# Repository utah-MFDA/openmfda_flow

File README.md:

# OpenMFDA (Microfluidic Design Automation) – Quick start
We are excited to help members of the community test and use this software. If you are interested we are happy to help you get started, please email ashton.snelgrove@utah.edu.

This document should help with providing setup and run the software flow for OpenMFDA with the
supplied code to run that smart toilet chip. For the most up to date version clone the repo at
https://github.com/utah-MFDA/openmfda_flow.

## Setup

### Submodules

If pulled from github, this repository contains submodule links to design kits and tools. Make
sure to run `git submodule update --init --recursive` after cloning or updating to ensure that
the submodules are up to date.

### Prerequisites Linux based systems

The following external tools are required.
- OpenROAD
- KLayout
- Xyce (7.8)
    - must be built from source with the ADMS plugin
    - ADMS (2.3.7)
- OpenSCAD
- python3
- make

The OpenROAD tool can be downloaded at https://github.com/The-OpenROAD-Project/OpenROAD.
Xyce can be built from https://github.com/Xyce/Xyce. Be sure to build with the ADMS plugin.

By default, the tools are invoked using the $PATH search variable.

Environment variables can be set to specify a specific location for the tools.

### Python environment

Python package dependencies can be installed using the system package manager, or using a virtual environment.
To create a virtual environment and install the tool dependencies, run the following commands.

```
python3 -m venv env
source env/bin/activate
pip3 install -r python-requirements.txt
```

This will create a directory `env` containing the python environment and libraries. To activate
the environment you will need to run `source env/bin/activate` before using the flow.
For more information about virtual environments, see https://docs.python.org/3/library/venv.html

## Prerequisites for Docker base implementation

We have a developed Docker based implementation for deployment that can work on
non-linux systems.

### Software requirements
- Docker
    - Recommended: https://docs.docker.com/desktop/
- WSL
    - https://learn.microsoft.com/en-us/windows/wsl/install
- Python3
- Recommended: OpenSCAD

## Running the flow

### Linux based systems

Once configured (as demonstrated in the next section), the flow is invoked with the `make` command.

Specifying the design
The design being operated on is specified using the `DESIGN` variable, matching the design
name used during configuration. This can be set by:

- The design can be specified when invoking `make`, for example `make DESIGN=smart_toilet`.
- The design can be specified once in an environment variable `export DESIGN=smart_toilet`,
	then subsequent invocations using `make -e`.
- The `DESIGN` variable can be set in the `Makefile` in the root of the directory.

### Running the flow

To run the complete flow, invoke `make` (with the design variable specified as shown in the previous section).
This will run all steps in the flow and generate a .zip archive containing all output files.

To run placement and routing, invoke `make pnr`

To generate the device 3D model, invoke `make render`

To generate flow analysis files of the design, invoke `make simulate`

To remove all generated files, invoke `make clean`

## For non-linux based system - Docker based implementation

For non-linux based system a script to run the flow within a docker image with the necessary software is provided.
This must be run within a windows WSL shell (a linux shell within windows) for windows systems, instructions
to install WSL on windows can be found at, https://learn.microsoft.com/en-us/windows/wsl/install

To get started you can simply run the command:

```
python3 run_mfda_docker.py –design smart_toilet
```

This will, in not already, download the docker image, and run the demo, smart toilet chip, design.
The Docker image will contain the necessary software and python packages to run the flow.

# Configuration

## Quick start configuration

Place your verilog netlist in the root directory of the flow.

Create a copy of the `demo_configure.py` script or create a new file with the following.

```
from openmfda_flow import *

verilog_file = "demo.v"
design_name = "demo"
platform = "h.r.3.3"
pins = [[None for i in range(0,8)] for j in range(0,4)]
pins[0][1] = "soln1"
pins[0][2] = "soln2"
pins[0][3] = "soln3"
pins[1][7] = "out"

generate_config(verilog_file, design_name, pin_names=pins, platform=platform)
```

Modify your copy, specifying the `verilog_file` and `design_name`.

For each input/output pins from your verilog file, add an entry in the array in row/column format. This will assign the pin to the port of the interface.

Invoke your script like `python3 demo_configure.py`, which will generate configuration files.

After the configuration is created, the flow can be run by invoking `make DESIGN=demo`.

Once configured, verilog design and configuration files can be modified as described in the next section. Verilog files are located in `openroad_flow/designs/src/{DESIGN}`

## Manual configuration

To manually configure a flow, the following steps are taken:

1. Start by creating a new design with this path structure
    - openroad_flow/designs/(platform)/(design name)
2. Within the folder above, three files need to be generated:
   ./config.mk, ./constraint.sdc, and ./io_constraints.tcl.
   Designs are included for reference.
    - ./config.mk - this contains variables that specify the
      design name, platform, relevant design paths, and floor
      planning parameters such as die size (MF chip size) and
      core size (legal placement and route area).
    - ./constraint.sdc - only contains the design name.
      Critical file in EDA but not used in the current flow of
      MFDA.
    - ./io_constraints.tcl - this specifies where the I/Os of
      the MF chip are physically located. If using the
      flushing chip automatically generated in the flow, the
      I/Os must be configured such as in
      /openroad_flow/designs/mfda/smart_toilet/io_constraints.tcl
      for correct allignment with the flushing chip. Otherwise,
      the I/Os must be placed at the edge of the device and
      pinholes will automatically added for tubing.
3. The chips are described using Verilog HDL netlist scripting.
   The netlist description is structured like
   /openroad_flow/designs/src/(design)/(design).v.
   This netlist describes the I/Os, what components are used,
   and how they are all connected.
4. In /openroad_flow/Makefile, the *DESIGN_CONFIG* variable
   must be the path to the /config.mk file described in step 2.
5. The 3D configuration is setup in this path structure,
   /scad_flow/designs/(platform)/(design name). Within
   this folder are two files: ./config.mk and the optional file
   ./dimm.csv.
   - ./config.mk - This file contains several variable that
     specify the 3D parameters of the MF chip as well as the printer
     properties such as physical pixel and layer size.
   - ./dimm.csv - this is an optional file which specifies dimensions
     for the interconnect channels between components and I/Os. The format
     should be as follows:
     ```
     For component and I/O interconnects:

     pin_name,horizontal_channel_width,vertical_channel_width,channel_height

     For I/Os (connecting to the flushing chip through the interconnect device):

     pin_name,square_side_width
     ```
     All widths are integer number of pixels and heights are integer number of
     layers.
6. After all the files are added for the design with the
   parameters specified, the entire flow can be completed through
   the Makefile in /Makefile
   ```
   make DESIGN=demo
   ```

## Expected output

We expect during program runtime that the terminal will print the logs for each of
the steps to be completed in the program. Several design files for each step of the
physical design process will be in the `flow/results/<design_name>/base` directory.
The final .scad file that is located in the `flow/results/<design_name>/base` which will
be named `<name of your design>_base.scad` can be loaded into OpenSCAD to render the final
results. The simulation evaluation output will be inside the flow/results/simulation/Chem_Eval.csv`
directory and any probe data will be in `flow/results/simulation/<design_name>_xyceOut.csv`.

Instructions for use on submitted data
To run the program on the smart toilet data simply run.

```
cd flow && make -e DESIGN=smart_toilet
```

or for docker implementation

```
python3 run_mfda_docker.py -–design smart_toilet
```

Results should be located in the `flow/results/smart_toilet/base` directory.

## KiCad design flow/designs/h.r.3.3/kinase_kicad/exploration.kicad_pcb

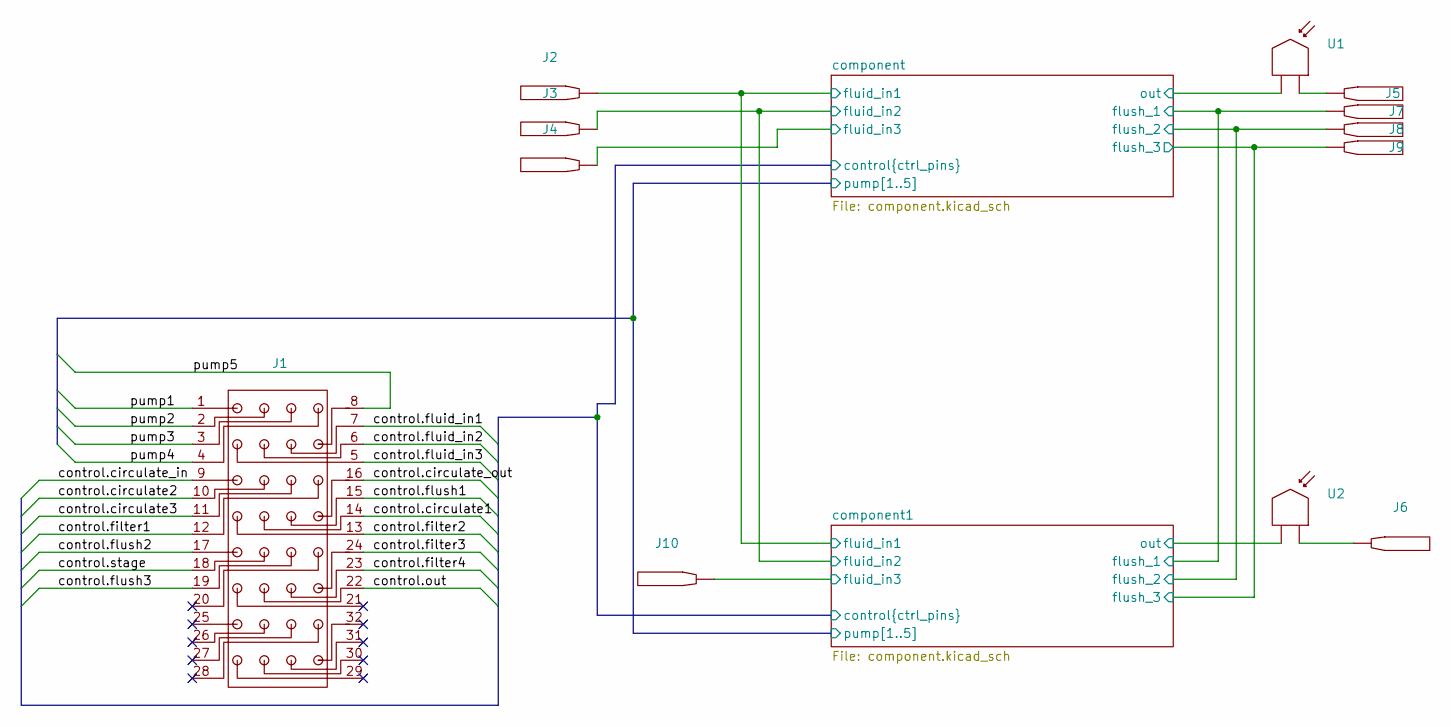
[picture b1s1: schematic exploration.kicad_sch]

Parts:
J1: LQFP-32_7x7mm_P0.8mm
J2, J3, J4, J5, J6, J7, J8, J9, J10: Pin_D1.0mm_L10.0mm
U1, U2: PinHeader_1x02_P2.54mm_Vertical

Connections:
/component1/fluid_in3: J10.1 (connect); also elsewhere on the board
/component1/out: U2.2 (out); also elsewhere on the board
/component/control.circulate1: J1.14; also elsewhere on the board
/component/control.circulate2: J1.10; also elsewhere on the board
/component/control.circulate3: J1.11; also elsewhere on the board
/component/control.circulate_in: J1.9; also elsewhere on the board
/component/control.circulate_out: J1.16; also elsewhere on the board
/component/control.filter1: J1.12; also elsewhere on the board
/component/control.filter2: J1.13; also elsewhere on the board
/component/control.filter3: J1.24; also elsewhere on the board
/component/control.filter4: J1.23; also elsewhere on the board
/component/control.fluid_in1: J1.7; also elsewhere on the board
/component/control.fluid_in2: J1.6; also elsewhere on the board
/component/control.fluid_in3: J1.5; also elsewhere on the board
/component/control.flush1: J1.15; also elsewhere on the board
/component/control.flush2: J1.17; also elsewhere on the board
/component/control.flush3: J1.19; also elsewhere on the board
/component/control.out: J1.22; also elsewhere on the board
/component/control.stage: J1.18; also elsewhere on the board
/component/fluid_in1: J2.1 (connect); also elsewhere on the board
/component/fluid_in2: J3.1 (connect); also elsewhere on the board
/component/fluid_in3: J4.1 (connect); also elsewhere on the board
/component/flush_1: J7.1 (connect); also elsewhere on the board
/component/flush_2: J8.1 (connect); also elsewhere on the board
/component/flush_3: J9.1 (connect); also elsewhere on the board
/component/out: U1.2 (out); also elsewhere on the board
/component/pump1: J1.1; also elsewhere on the board
/component/pump2: J1.2; also elsewhere on the board
/component/pump3: J1.3; also elsewhere on the board
/component/pump4: J1.4; also elsewhere on the board
/component/pump5: J1.8; also elsewhere on the board
unnamed: J5.1 (connect), U1.1 (in)
unnamed: J6.1 (connect), U2.1 (in)

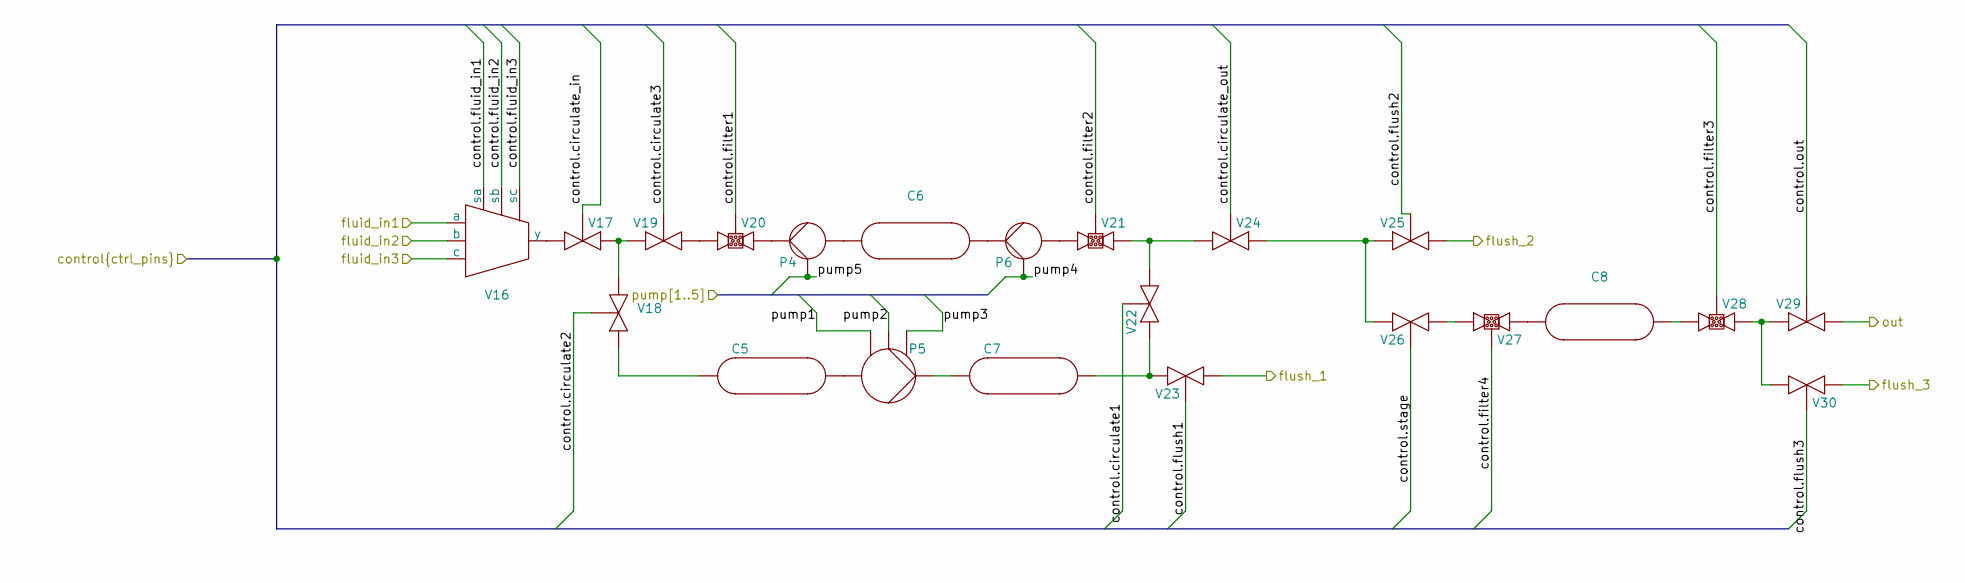
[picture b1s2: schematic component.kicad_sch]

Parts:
C5, C6, C7, C8: R_2010_5025Metric
P4, P6: PinHeader_1x03_P2.54mm_Vertical
P5: PinHeader_1x05_P2.54mm_Vertical
V16: HSOP-8-1EP_3.9x4.9mm_P1.27mm_EP2.41x3.1mm_ThermalVias
V17, V18, V19, V20, V21, V22, V23, V24, V25, V26, V27, V28, V29, V30: Potentiometer_ACP_CA6-VSMD_Vertical

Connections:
/component1/fluid_in3: V16.3 (c); also elsewhere on the board
/component1/out: V29.2 (right); also elsewhere on the board
/component/control.circulate1: V22.3 (control); also elsewhere on the board
/component/control.circulate2: V18.3 (control); also elsewhere on the board
/component/control.circulate3: V19.3 (control); also elsewhere on the board
/component/control.circulate_in: V17.3 (control); also elsewhere on the board
/component/control.circulate_out: V24.3 (control); also elsewhere on the board
/component/control.filter1: V20.3 (control); also elsewhere on the board
/component/control.filter2: V21.3 (control); also elsewhere on the board
/component/control.filter3: V28.3 (control); also elsewhere on the board
/component/control.filter4: V27.3 (control); also elsewhere on the board
/component/control.fluid_in1: V16.4 (sa); also elsewhere on the board
/component/control.fluid_in2: V16.5 (sb); also elsewhere on the board
/component/control.fluid_in3: V16.6 (sc); also elsewhere on the board
/component/control.flush1: V23.3 (control); also elsewhere on the board
/component/control.flush2: V25.3 (control); also elsewhere on the board
/component/control.flush3: V30.3 (control); also elsewhere on the board
/component/control.out: V29.3 (control); also elsewhere on the board
/component/control.stage: V26.3 (control); also elsewhere on the board
/component/fluid_in1: V16.1 (a); also elsewhere on the board
/component/fluid_in2: V16.2 (b); also elsewhere on the board
/component/flush_1: V23.2 (right); also elsewhere on the board
/component/flush_2: V25.2 (right); also elsewhere on the board
/component/flush_3: V30.1 (left); also elsewhere on the board
/component/pump1: P5.3 (pump_1); also elsewhere on the board
/component/pump2: P5.4 (pump_2); also elsewhere on the board
/component/pump3: P5.5 (pump_3); also elsewhere on the board
/component/pump4: P6.3 (pump_1); also elsewhere on the board
/component/pump5: P4.3 (pump_1); also elsewhere on the board
unnamed: C5.1 (in), V18.1 (left)
unnamed: C5.2 (out), P5.1 (in)
unnamed: C6.1 (in), P6.2 (out)
unnamed: C6.2 (out), P4.1 (in)
unnamed: C7.1 (in), P5.2 (out)
unnamed: C7.2 (out), V22.1 (left), V23.1 (left)
unnamed: C8.1 (in), V27.1 (in)
unnamed: C8.2 (out), V28.2 (out)
unnamed: P4.2 (out), V20.1 (in)
unnamed: P6.1 (in), V21.2 (out)
unnamed: V16.7 (y), V17.2 (right)
unnamed: V17.1 (left), V18.2 (right), V19.1 (left)
unnamed: V19.2 (right), V20.2 (out)
unnamed: V21.1 (in), V22.2 (right), V24.2 (right)
unnamed: V24.1 (left), V25.1 (left), V26.1 (left)
unnamed: V26.2 (right), V27.2 (out)
unnamed: V28.1 (in), V29.1 (left), V30.2 (right)

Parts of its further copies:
C1, C2, C3, C4: R_2010_5025Metric
P1, P3: PinHeader_1x03_P2.54mm_Vertical
P2: PinHeader_1x05_P2.54mm_Vertical
V1: HSOP-8-1EP_3.9x4.9mm_P1.27mm_EP2.41x3.1mm_ThermalVias
V2, V3, V4, V5, V6, V7, V8, V9, V10, V11, V12, V13, V14, V15: Potentiometer_ACP_CA6-VSMD_Vertical

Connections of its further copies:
/component/control.circulate1: V7.3 (control); also elsewhere on the board
/component/control.circulate2: V3.3 (control); also elsewhere on the board
/component/control.circulate3: V4.3 (control); also elsewhere on the board
/component/control.circulate_in: V2.3 (control); also elsewhere on the board
/component/control.circulate_out: V9.3 (control); also elsewhere on the board
/component/control.filter1: V5.3 (control); also elsewhere on the board
/component/control.filter2: V6.3 (control); also elsewhere on the board
/component/control.filter3: V13.3 (control); also elsewhere on the board
/component/control.filter4: V12.3 (control); also elsewhere on the board
/component/control.fluid_in1: V1.4 (sa); also elsewhere on the board
/component/control.fluid_in2: V1.5 (sb); also elsewhere on the board
/component/control.fluid_in3: V1.6 (sc); also elsewhere on the board
/component/control.flush1: V8.3 (control); also elsewhere on the board
/component/control.flush2: V10.3 (control); also elsewhere on the board
/component/control.flush3: V15.3 (control); also elsewhere on the board
/component/control.out: V14.3 (control); also elsewhere on the board
/component/control.stage: V11.3 (control); also elsewhere on the board
/component/fluid_in1: V1.1 (a); also elsewhere on the board
/component/fluid_in2: V1.2 (b); also elsewhere on the board
/component/fluid_in3: V1.3 (c); also elsewhere on the board
/component/flush_1: V8.2 (right); also elsewhere on the board
/component/flush_2: V10.2 (right); also elsewhere on the board
/component/flush_3: V15.1 (left); also elsewhere on the board
/component/out: V14.2 (right); also elsewhere on the board
/component/pump1: P2.3 (pump_1); also elsewhere on the board
/component/pump2: P2.4 (pump_2); also elsewhere on the board
/component/pump3: P2.5 (pump_3); also elsewhere on the board
/component/pump4: P3.3 (pump_1); also elsewhere on the board
/component/pump5: P1.3 (pump_1); also elsewhere on the board
unnamed: C1.1 (in), V3.1 (left)
unnamed: C1.2 (out), P2.1 (in)
unnamed: C2.1 (in), P3.2 (out)
unnamed: C2.2 (out), P1.1 (in)
unnamed: C3.1 (in), P2.2 (out)
unnamed: C3.2 (out), V7.1 (left), V8.1 (left)
unnamed: C4.1 (in), V12.1 (in)
unnamed: C4.2 (out), V13.2 (out)
unnamed: P1.2 (out), V5.1 (in)
unnamed: P3.1 (in), V6.2 (out)
unnamed: V1.7 (y), V2.2 (right)
unnamed: V2.1 (left), V3.2 (right), V4.1 (left)
unnamed: V4.2 (right), V5.2 (out)
unnamed: V6.1 (in), V7.2 (right), V9.2 (right)
unnamed: V9.1 (left), V10.1 (left), V11.1 (left)
unnamed: V11.2 (right), V12.2 (out)
unnamed: V13.1 (in), V14.1 (left), V15.2 (right)

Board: 2 copper layers, 56 parts (0 on the bottom side), 67 nets, no tracks yet.

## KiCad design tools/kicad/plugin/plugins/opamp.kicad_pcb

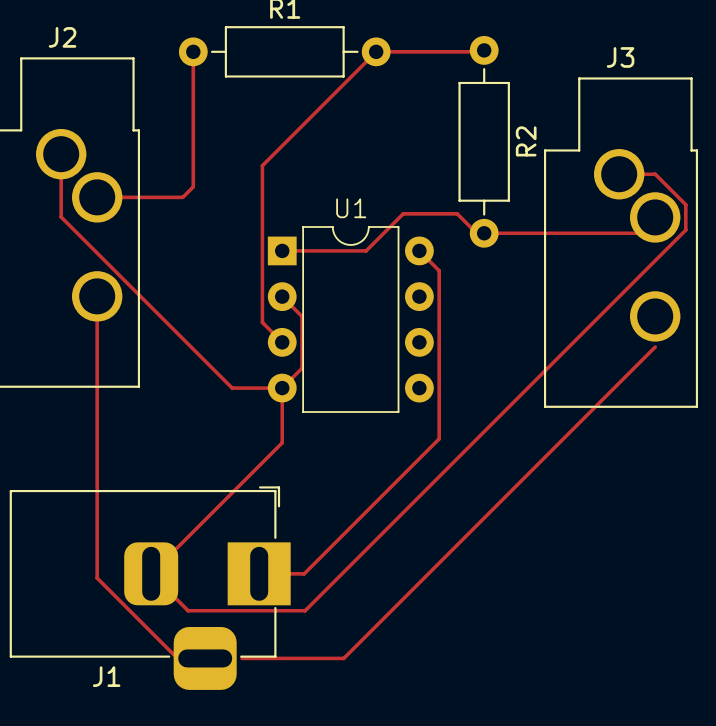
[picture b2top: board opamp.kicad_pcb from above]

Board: 2 copper layers, 6 parts (0 on the bottom side), 5 nets.

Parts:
J1: Barrel_Jack; BarrelJack_Horizontal
J2, J3: AudioJack2; Jack_3.5mm_CUI_SJ1-3533NG_Horizontal_CircularHoles
R1, R2: 100k; R_Axial_DIN0207_L6.3mm_D2.5mm_P10.16mm_Horizontal
U1: TL072; DIP-8_W7.62mm

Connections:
+5V: J1.1, U1.8 (V+)
/result: J3.T, R2.2, U1.1
/signal: J2.T, R1.1
GND: J1.2, J2.S, J3.S, U1.2 (-), U1.4 (V-)
unnamed: R1.2, R2.1, U1.3 (+)

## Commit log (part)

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2024-06-07 python version
2024-06-07 demo with all replace vars
2024-06-07 local updates
2024-06-07 update writeSpice to master
2024-06-10 fix scad sign bug
2024-06-10 Initial kicad network parsing
2024-06-10 Add simulation to flow makefile
2024-06-11 Latest fixes to HR33 pdk
2024-06-13 Complete flow working with simulation and library building
2024-06-13 Basic kicad schematic netlist extraction.
2024-06-18 Initial conversion script from DEF to kicad board.
2024-07-10 src formating and git mods del
2024-07-10 testing platform and OR changes
2024-08-07 major simulation changes, dimm_file ref fixes, openmfda_flow.py changes
2024-08-09 major fixes to generator class
2024-08-27 pcell module and xyce code fixes
2024-08-27 Add pcbnew based conversion scripts
2024-08-28 WX exploration
2024-09-12 Create script to generate kicad footprint library from LEF files.
2024-09-12 Remove debugging and local configuration from lef_to_footprint.
2024-09-12 Remove local test config for main in def_to_pcbnew and def_to_board
2024-09-18 fixes to xyce_flow and scad_flow
2024-09-18 changes to openmfda_class
2024-09-19 join '_' fix to runMFDASim
2024-09-19 OR parsing files
2024-09-20 Add scripts to generate a platform with different number of metal layers.
2024-09-20 Make log directories for our tools actually go to the logs directory.
2024-09-26 init pkg on main branch
2024-10-17 various tool fixes, scad_gen
2024-10-22 Remove reference to networkx
2024-10-24 Fix argparse for consistency in kicad scripts
2024-10-24 Formatting text for kicad footprint generator.
2024-10-25 Set the text type to 'user' for the pin labels when converting footprint.
2024-10-25 Cleaning and fixed hard coded definitions
2024-10-26 merged with fixed version of generator render
2024-11-01 update to submodules
2024-11-01 py src changes and updates to PCell definitions
2024-11-01 added extra scad files to include in the flow
2024-11-04 changes to pcell config.mk
2024-11-05 Added PCELL as dep to floorplan
2024-11-12 Get the correct field from pcbnew for the footprint id in pcbnew-to-verilog
2024-11-20 Remove missing submodule in tools/simulation
2024-11-20 Use correct layer height variable in slicer configuration.
2024-12-05 Update tcl scripts to handle a macro and pad placement scripts
2024-12-05 Setup kinase_activity 2 variant to use explicitly placed chambers and pads.
2024-12-10 Update submodules to fix broken inner modules.
2025-01-10 WIP plugin
2025-01-17 Kinase example macro and pad placement using latest openroad commands.
2025-01-21 WIP export happy: :
2025-01-22 WIP PNR working.
2025-01-23 updates to render gen v2 and helper scripts
2025-01-31 Add kicad page offset
2025-01-31 Add xvfb command variable.
2025-01-31 Create kicad layer names and vias use correct ids.
2025-02-03 Added intersection detection, rm unneeded comments
2025-02-03 devel changes for main flow
2025-02-03 now tracks a stable branch
2025-02-03 def load and export functions, changes to iteration implementation
2025-02-04 Write locked Kicad footprints as explicit placed macro.
2025-02-04 Remove report call missing from latest openroad.
2025-02-06 Fix orientation in the lef to kicad footprint conversion script.
2025-02-10 Update kinase_activity_2 to use new openroad syntax and switch from bump pad to pin. Bump pads generate but special nets are not routed.
2025-02-10 Switch to Brady's scad generator, which is most up to date with pdk changes.
2025-03-15 addition to tcl scripts, fixes to py code
2025-04-14 Lots of clean up, more examples. Added Docker implementation
2025-04-17 write out def
2025-04-18 Added make script
2025-04-21 v0.1 of route fix
2025-04-24 Fix to pcell gen
2025-04-28 Files prior to updating tools/scad_render directory
2025-04-29 Working flow with Python script, issues with Tcl implmentation
2025-05-06 fixes to silent, small mk file chg, src mnt docker
2025-05-07 update to simulation
2025-05-08 Parse verilog models
2025-05-23 DEF_FIX changes
2025-05-29 fixes to replace iter
2025-06-04 grt script fix with added pin and routing size def to scad
2025-06-04 fixed routing size arg
2025-06-17 fix simulation branch ref and gitmodules reference
2025-06-17 Fixed Makefile ref for simulation
2025-06-17 updated component file
2025-06-22 inluded some support python code, and old lef lib
2025-06-22 update pdk ref, lib link fix, test script fix
2025-06-26 fixes to req and update docs
2025-06-26 small run_dock fix
2025-07-03 WIP fixing sizes
2025-07-03 WIP fix pins
2025-07-07 Fix user_arg string
2025-07-29 Added documentation for the flow pdk
2025-07-29 Change tracked pdk to lib 0.0.2
2025-07-29 no tracking of lock files
2025-07-30 Moved 3D printer definitions to sperate file, config_3dp.mk
2025-08-04 Updated README, added pdk docs, and template platform
2025-08-28 Cleanup WIP
2025-08-28 Initial ILP 3d formulation.
2025-08-29 ILP formulation works slowly for <10 nodes but dies on larger.
2025-09-03 add comments makefile and config name and link
2025-09-03 update to run_mfda_docker
2025-09-04 Python script for modifying and rebuilding component library pieces based on printer parameters.
2025-09-04 Added all files to run urinalysis design automation into own folder. Place files in main directory to run properly.
2025-09-04 Removed urinalysis design automation files from main directory and put in own subdirectory
2025-09-05 Attempt at a frontier exploring shell placement
2025-09-05 Updated junction geometry
2025-09-05 3D routing by shell is at least running, constraints aren't correct
2025-09-08 WIP, works for half of the graph.
2025-09-10 Working version with relaxed constraints.
2025-09-17 Modified diffmix_25px and junction_25px mirroring logic to minimize routing issues with orientation changes
2025-09-24 Update json graph extraction to pull metadata
2025-09-24 Remove some extraneous kinase benchmark files.
2025-09-26 Refactor everything
2025-09-29 Migrate network type checks to the helper module.
2025-09-29 Working hypergraph reader
2025-09-29 Consolidate naming to cylinder
2025-09-29 Fixed whatever was failing
2025-09-30 Extract target and source calculation up a level
2025-09-30 Fix direction of numeric check
2025-10-02 Add an experiment in a complete single pass solve
2025-10-02 Consolidate coordinate storage
2025-10-02 Conslidate the slice bound functions to generalized
2025-10-06 Refactor to add argparse
2025-10-07 Remove committed scad files.
2025-10-07 Switch to argeparse flags in makefile
2025-10-07 Improve scad rendering output organizaton
2025-10-07 Remove redundant horizontal version of bounding
2025-10-08 Fix argument order for bounding function
2025-10-09 fixes to global_route.tcl, merge tlef with kicad
2025-10-09 Add option to skip non-flow nodes
2025-10-10 Add option to collapse non-hyperedges
2025-10-10 Add missing edge properties
2025-10-10 Implement peer relationships and add a switch to do minimization of relaxation
2025-10-10 Clean up logging message
2025-10-10 Add a runner which backtracks. Doesn't really work.
2025-10-15 Makefile files post merge
2025-10-15 removed need for python-regex
2025-10-15 SCAD_LIB in Makefile, fixes to re-iter
2025-10-15 modified kicad files
2025-10-16 cleaned up interfaces, build-all added
2025-10-16 add SITES to h.r.3.3_0.0.2.tlef
2025-10-16 fix link merge lef h.r.3.3
2025-10-20 rm git added lines
2025-10-22 Add dimensional reduction script prototype.
2025-10-23 Auto-place pcdnew 4x8 interface
2025-10-23 Checking what PCA does out of the box.
2025-10-23 Add some vars to makefile,
2025-10-25 Initial kicad server plugins
2025-10-27 WIP on server testing
2025-10-28 Final directories and configurartion for server.
2025-10-28 Update simulation submodule
2025-10-28 Remove broken relative import
2025-10-28 Kicad server passing data down without crashing
2025-10-28 Server plugin implementation
2025-10-28 Fix configuration generation
2025-10-28 Plugin layout cleanup
2025-10-28 Fix typos
2025-10-28 Move plugin files into a location which can be directly zipped
2025-10-28 Really good results from existing dimensional reduction algorithms
2025-10-29 Dev-kcad fixes, edits to scripts for new flow and rm padring for now
2025-10-31 Fix symlinks between kicad server directory and plugin.
2025-10-31 Fix pathing issues in kicad server
2025-11-01 Move kicad-dev over kicad to prepare for merge
2025-11-04 add help contact info.
2025-11-11 Make rendering more generic with color selection
2025-11-11 Handle multigraph in networkx helpers
2025-11-11 Change skip and buffer conditions
2025-11-11 Cleanup and optiomize dimension reduction
2025-11-11 Add constraints separate from solving
2025-11-12 Update benchmarks with parameterized versions
2025-11-12 Update benchmarks for 3d routing
2025-11-12 Add a csv cache/output
2025-11-13 Configurable log file
2025-11-13 Add an all at once horizontal mode
2025-11-13 Ran experiments with shorter bound distance and catching inout ports as init conditions.
2025-11-13 Update kinase benchmark
2025-11-13 Add pad versions of mnacidpro and mrnaiso
2025-11-16 Add a shared optimization variable for bounding
2025-11-16 Update results"
2025-11-16 Change some settings in makefile.
2025-11-16 Call out to subprocess to run scip to try and avoid memory issues
2025-11-16 Extract stats and log during solve
2026-01-14 Suquential multiplex Verilog file
2026-01-22 added routing script to tools, add documenting and logs
2026-02-27 fixes to scad render graph build
2026-03-23 fixes to pin detection
2026-03-23 checkout scad_render from bgoe_dev
2026-03-25 Fixed graph building, needs more updates
2026-04-03 include def_load in scad render
2026-04-03 Allows for rendering of specific def through make
2026-04-15 h.r.3.3x2 platform - double the die area space of h.r.3.3
2026-05-05 OpenMFDA+ files: urinalysis design automation and general class of continuous-flow, pressure-driven chips
2026-05-12 New platform, h.r.3.3x2. Has double the die area than h.r.3.3
2026-05-12 Urinalysis multiplex device
2026-05-12 Removed urinalysis design automation files. This branch is for the development of the Phrozen pdk. The urinalysis files can be found on the urinalysis suite automation branch
2026-05-12 Files for automating the an individual urinalysis design. Currently being modified to accomodate for the more complex multiplex chip. Design information is now read in from multiplex.json, as opposed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
2026-05-19 config.mk file that utilizes h.r.3.3_merged.scad rather than components.scad
2026-05-19 Modifications for p_resistor to be recognized by OpenMFDA in designs. 'dr' variable currently has issues being recognized by verilog_param_preaparse.py
2026-05-22 Pulling files for h.r.3.3x2 (double die area) platform
2026-05-22 Modifications to files before switching branch
2026-05-22 File modifications before switching branches
2026-05-27 Catch up of mfda work, py efforts and scad render
2026-05-27 fixes to pysrc rm main dir
2026-05-28 single file merge with phrozen_lib
2026-05-28 Updates from Brady's development branch
2026-05-28 Getting simulation errors for mutliplex_test design on h.r.3.3x2 printer
2026-05-29 Files to run test design
2026-05-29 Urinalysis automation results
2026-06-01 Updated io_file function in file_generation.py
2026-06-02 Modifications to library_adjust.py to account for new platform setup
2026-06-02 Working simulation for p_resistor component
2026-06-03 Updated file_generation.py functions for multiplex definition
2026-06-04 Updated files to automatically generate necessary files needed to automate mutliplex design (minus routing.csv)
2026-06-05 update to simulation to latest
2026-06-08 Brady's updates to tools/scad_render
2026-06-08 Updates to tools/simulation from Brady's development branch
2026-06-12 Added simulation subckt support
2026-06-15 Automated creation of routing.csv with channel dimensions of w_chan, w_chan, and h_chan
2026-06-16 Modifications to sim_eval_files and con_results functions to keep track of R# assigned to each input and corresponding concentration errors
2026-06-17 Modifications to newton_method, edit_file, and update_flow functions to account for multiplex definition and to allow for modifications of multiple components at a time
2026-06-22 Traditional Newton-Raphson and Biscetion methods that update one component at a time
2026-06-22 Updated simulation .so file
2026-06-24 Iterative OpenMFDA flow adjustments for multiplex device. Completes placement, routing, and rendering but has errors in simulation
2026-06-24 Modifications to make_file function for update_flow function to work
